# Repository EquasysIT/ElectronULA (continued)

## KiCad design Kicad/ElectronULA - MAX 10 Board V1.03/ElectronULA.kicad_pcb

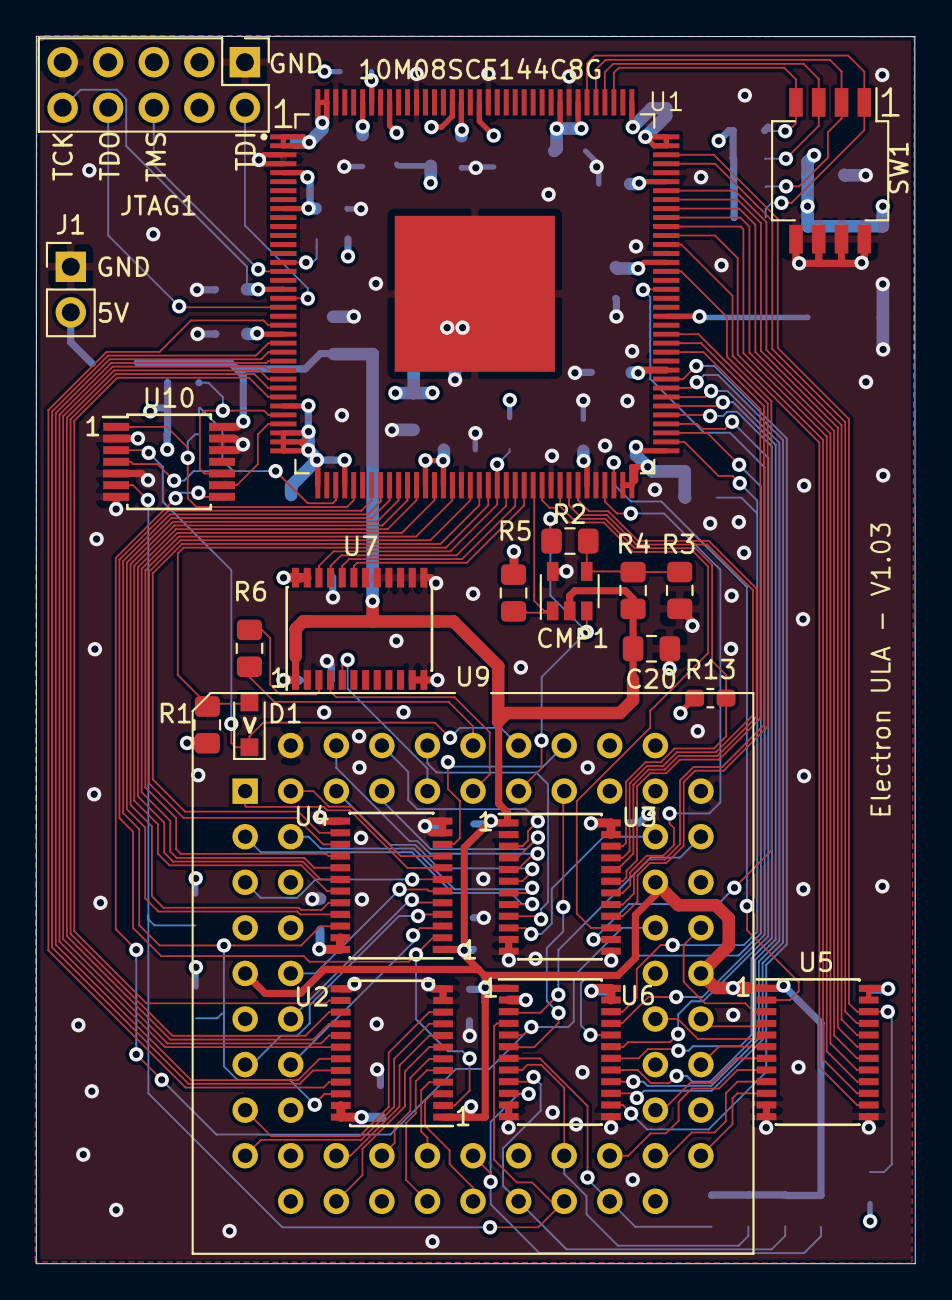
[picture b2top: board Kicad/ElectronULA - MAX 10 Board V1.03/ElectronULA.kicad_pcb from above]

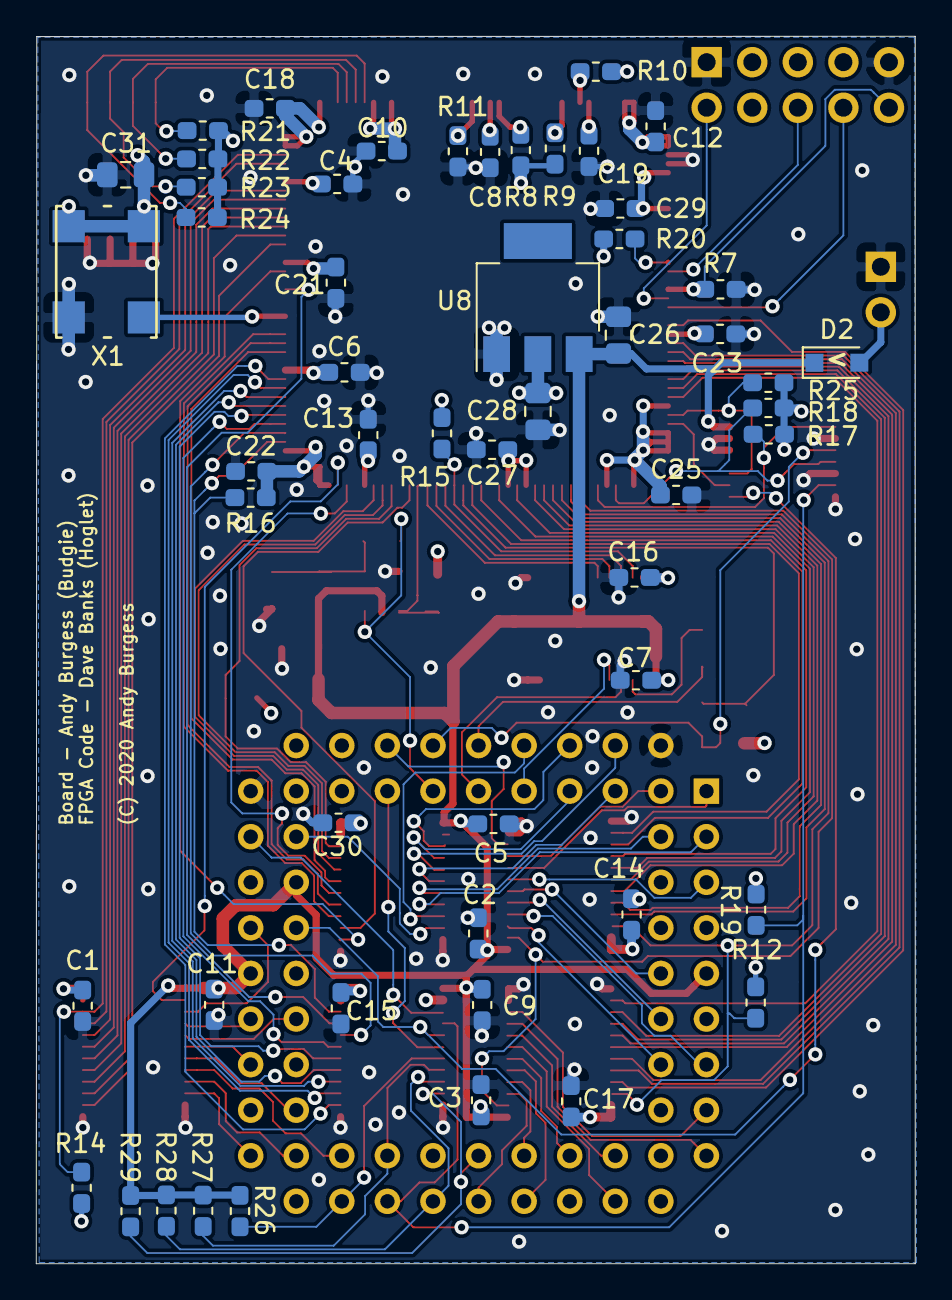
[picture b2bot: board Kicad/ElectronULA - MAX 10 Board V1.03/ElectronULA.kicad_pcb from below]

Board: 4 copper layers, 49.0 x 68.4 mm, 76 parts (54 on the bottom side), 121 nets.

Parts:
C1, C2, C3, C4, C5, C6, C7, C8, C9, C10, C11, C12, C13, C14, C15, C16, C17, C18, C19, C21, C22, C23, C25, C27, C29, C30: 0.1uf; C_0603_1608Metric_Pad1.05x0.95mm_HandSolder
C20: 0.1uf; C_0805_2012Metric_Pad1.15x1.40mm_HandSolder
C26, C31: 0.1uF; C_0805_2012Metric_Pad1.15x1.40mm_HandSolder
C28: 10uF; C_0805_2012Metric_Pad1.15x1.40mm_HandSolder
CMP1: MIC7221YM5-TR; SOT-23-5
D1, D2: D_Schottky_Small; D_SOD-323_HandSoldering
J1: Conn_01x02; PinHeader_1x02_P2.54mm_Vertical
JTAG1: Conn_02x05_Odd_Even; PinHeader_2x05_P2.54mm_Vertical
R1, R2, R3, R4, R5: 10K; R_0805_2012Metric_Pad1.15x1.40mm_HandSolder
R6: 100; R_0805_2012Metric_Pad1.15x1.40mm_HandSolder
R7, R8, R9, R10, R11, R12, R13, R14, R15, R16, R17, R18, R19, R20, R21, R22, R23, R24, R25: 10K; R_0603_1608Metric_Pad1.05x0.95mm_HandSolder
R26, R27, R28, R29: 4.7K; R_0603_1608Metric_Pad1.05x0.95mm_HandSolder
SW1: SW_DIP_x04; SW_DIP_SPSTx04_Slide_Copal_CHS-04B_W7.62mm_P1.27mm
U1: 10M08SCE144C8G; QFP50P2200X2200X165-145N
U2, U3, U4, U5, U6, U7: 74LVC4245APW; TSSOP-24_4.4x7.8mm_P0.65mm
U8: AP111733; SOT-223
U9: ELECTRON_ULA_PGA_68; PLCC-68_THT-Socket-Electron-ULA
U10: SN74HCT125D; TSSOP-14_4.4x5mm_P0.65mm
X1: OSC; Crystal_SMD_7050_4Pads

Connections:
/3V3: C1.1, C4.1, C6.1, C8.1, C10.1, C12.1, C13.1, C14.1, C15.1, C16.1, C17.1, C18.1, C19.1, C21.1, C22.1, C23.1, C25.1, C27.1, C28.1, C29.1, C30.1, C31.1, JTAG1.7, R1.2, R5.2, R8.1, R9.1, R10.1, R12.2, R13.2, R14.1, R15.2, R16.1, R17.2, R18.2, R19.2, R20.1, R21.2, R22.2, R23.2, R24.2, R25.2, U1.1, U1.2, U1.5, U1.9, U1.23, U1.31, U1.34, U1.35, U1.36, U1.37, U1.40, U1.49, U1.51, U1.67, U1.71, U1.72, U1.73, U1.82, U1.94, U1.103, U1.107, U1.108, U1.109, U1.115, U1.117, U1.128, U1.139, U1.143, U1.144, U2.23, U2.24, U3.23, U3.24, U4.23, U4.24, U5.23, U5.24, U6.2, U6.23, U6.24, U7.23, U7.24, U8.2, X1.1, X1.4
/5V: C2.1, C3.1, C5.1, C7.1, C9.1, C11.1, C20.2, C26.1, CMP1.2, D2.1, R4.2, R26.2, R27.2, R28.2, R29.2, U2.1, U3.1, U4.1, U5.1, U6.1, U7.1, U8.3, U9.9, U9.43, U9.48, U10.14
/5VP: D2.2, J1.2
/A0: U4.7, U9.5
/A1: U4.8, U9.1
/A2: U4.5, U9.12
/A3: U2.5, U9.24
/A4: U2.8, U9.21
/A5: U2.7, U9.20
/A6: U2.9, U9.17
/A7: U2.10, U9.15
/A8: U4.9, U9.2
/A9: U2.3, U9.26
/A10: U2.4, U9.25
/A11: U2.6, U9.23
/A12: U4.4, U9.13
/A13: U4.3, U9.14
/A14: U4.6, U9.10
/A15: U4.10, U9.56
/A_DIR: U1.43, U2.2, U4.2
/A_OE: R12.1, U1.44, U2.22, U4.22
/BLUE: U3.5, U9.66
/CAPS: U7.5, U9.63
/CASIN: CMP1.3, R2.1, U9.59
/CASMO: U3.3, U9.64
/CAS_OUT: U3.10, U9.50
/CLK_IN: U6.3, U9.49
/CONFIG_SEL: R11.2, U1.126
/CONF_DONE: R10.2, U1.138
/CSYNC: U3.4, U9.65
/G1_OE: R13.1, U1.64, U3.22
/G3_OE: R15.1, U1.57, U7.22
/G4_OE: R16.2, U1.74, U6.22
/GND: C1.2, C2.2, C3.2, C4.2, C5.2, C6.2, C7.2, C8.2, C9.2, C10.2, C11.2, C12.2, C13.2, C14.2, C15.2, C16.2, C17.2, C18.2, C19.2, C20.1, C21.2, C22.2, C23.2, C25.2, C26.2, C27.2, C28.2, C29.2, C30.2, C31.2, CMP1.5, J1.1, JTAG1.1, JTAG1.9, R3.1, R7.1, R11.1, SW1.5, SW1.6, SW1.7, SW1.8, U1.3, U1.4, U1.42, U1.53, U1.63, U1.68, U1.83, U1.95, U1.104, U1.116, U1.125, U1.133, U1.137, U1.142, U1.145, U2.11, U2.12, U2.13, U3.2, U3.11, U3.12, U3.13, U4.11, U4.12, U4.13, U5.11, U5.12, U5.13, U6.11, U6.12, U6.13, U7.2, U7.11, U7.12, U7.13, U7.14, U7.15, U7.16, U7.17, U7.18, U8.1, U9.51, U9.68, U10.2, U10.5, U10.7, U10.12, U10.13, X1.2
/GREEN: U3.7, U9.4
/JTAGEN: R20.2, U1.15
/KBD0: R29.1, U6.10, U9.27
/KBD1: R28.1, U6.9, U9.28
/KBD2: R27.1, U6.8, U9.31
/KBD3: R26.1, U6.7, U9.32
/LVA0: U1.50, U4.17
/LVA1: U1.52, U4.16
/LVA2: U1.47, U4.19
/LVA3: U1.25, U2.19
/LVA4: U1.28, U2.16
/LVA5: U1.27, U2.17
/LVA6: U1.29, U2.15
/LVA7: U1.30, U2.14
/LVA8: U1.54, U4.15
/LVA9: U1.22, U2.21
/LVA10: U1.24, U2.20
/LVA11: U1.26, U2.18
/LVA12: U1.46, U4.20
/LVA13: U1.45, U4.21
/LVA14: U1.48, U4.18
/LVA15: U1.55, U4.14
/LVBLUE: U1.84, U3.19
/LVCAPS: U1.60, U7.19
/LVCASIN: CMP1.1, R5.1, U1.61
/LVCASMO: U1.65, U3.21
/LVCAS_OUT: U1.93, U3.14
/LVCLK_IN: U1.91, U6.21
/LVCSYNC: U1.66, U3.20
/LVGREEN: U1.85, U3.17
/LVKBD0: U1.81, U6.14
/LVKBD1: U1.80, U6.15
/LVKBD2: U1.79, U6.16
/LVKBD3: U1.78, U6.17
/LVPD0: U1.98, U5.16
/LVPD1: U1.96, U5.14
/LVPD2: U1.97, U5.15
/LVPD3: U1.99, U5.17
/LVPD4: U1.100, U5.18
/LVPD5: U1.102, U5.20
/LVPD6: U1.101, U5.19
/LVPD7: U1.105, U5.21
/LVPHIOUT: U1.58, U7.21
/LVRED: U1.86, U3.16
/LVROM: U1.59, U7.20
/LVRSTOUT: R17.1, U1.41, U10.1
/LVRnWIN: U1.76, U6.19
/LVRnWOE: R25.1, U1.32, U10.10
/LVRnWOUT: U1.33, U10.9
/LVSND: U1.62, U3.15
/LVnHS: U1.69, U3.18
/LVnIRQIN: U1.75, U6.20
/LVnIRQOUT: R18.1, U1.39, U10.4
/LVnNMI: U1.77, U6.18
/OSC: U1.88, X1.3
/PD0: U5.8, U9.33
/PD1: U5.10, U9.35
/PD2: U5.9, U9.36
/PD3: U5.7, U9.38
/PD4: U5.6, U9.39
/PD5: U5.4, U9.41
/PD6: U5.5, U9.42
/PD7: U5.3, U9.45
/PD_DIR: U1.70, U5.2
/PD_OE: R14.2, U1.106, U5.22
/PHIOUT: R6.2, U9.60
/RED: U3.8, U9.3
/RESET: D1.1, U9.58, U10.3
/ROM: U7.4, U9.61
/RnW: U6.5, U9.46, U10.8
/SND: U3.9, U9.62
/SWC1: R24.1, SW1.1, U1.114
/SWC2: R23.1, SW1.2, U1.113
/SWC3: R22.1, SW1.3, U1.112
/SWC4: R21.1, SW1.4, U1.111
/TCK: JTAG1.10, R7.2, U1.18
/TDI: JTAG1.2, U1.19
/TDO: JTAG1.8, U1.20
/TMS: JTAG1.6, U1.16
/nCONFIG: R8.2, U1.129
/nHS: U3.6, U9.67
/nIRQ: R19.1, U6.4, U9.30, U10.6
/nNMI: U6.6, U9.57
/nRSTIN: D1.2, R1.1, U1.56
/nSTATUS: R9.2, U1.136
unnamed: CMP1.4, R2.2, R3.2, R4.1
unnamed: R6.1, U7.3

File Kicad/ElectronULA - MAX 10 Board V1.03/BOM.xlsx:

Acorn Electron ULA - MAX 10 Board - V1.03
Bill of Materials
Note: This board can only be fitted to a PGA68 socket on the Electron board. Th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
https://www.ebay.co.uk/i/292483310138?chn=ps&norover=1&mkevt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
Tips
1. Fit the ULA socket pins last (15). I would recommend "tinning" the pins whic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
2. Soldering the MAX 10 FPGA - Place a small amount of solder paste on the larg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
3. I recommend using a gel like flux for the SMD chips. Run plenty along each r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
4. All the passives (capacitors, resistors), comparator and regulator etc are b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
Excellent drag soldering guide here "https://www.youtube.com/watch?v=nyele3CIs-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
Id | Designator | Package | Quantity | Designation | Description | Supplier and ref
1 | R29,R28,R27,R26 | R_0603_1608Metric_Pad1.05x0.95mm_HandSolder | 4 | 4.7K Resistor | Pullups for Keyboard input
2 | D2,D1 | D_SOD-323_HandSoldering | 2 | Schottky Diode | BAT54 | https://www.digikey.co.uk/product-detail/en/on-semiconductor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
3 | U10 | TSSOP-14_4.4x5mm_P0.65mm | 1 | 74HCT125D | Quad Buffer | https://www.digikey.co.uk/product-detail/en/nexperia-usa-inc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,118/172…
4 | R25,R20,R24,R23,R22,R21,R19,R18,R17,R16,R15,R14,R13,R12,R11,R10,R9,R8,R7 | R_0603_1608Metric_Pad1.05x0.95mm_HandSolder | 19 | 10K Resistor
5 | SW1 | SW_DIP_SPSTx04_Slide_Copal_CHS-04B_W7.62mm_P1.27mm | 1 | SW_DIP_x04 | Configuration Switch | https://www.digikey.co.uk/product-detail/en/nidec-copal-elec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
6 | J1 | PinHeader_1x02_P2.54mm_Vertical | 1 | Conn_01x02 | 5V Power Input Normal Square Pins
7 | JTAG1 | PinHeader_2x05_P2.54mm_Vertical | 1 | Conn_02x05_Odd_Even | JTAG Pins Normal Square Pins
8 | C29,C27,C25,C23,C22,C21,C19,C18,C13,C12,C10,C8,C6,C4,C9,C7,C5,C3,C2,C11,C16,C30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 | C_0603_1608Metric_Pad1.05x0.95mm_HandSolder | 26 | 0.1uf Capacitor
9 | X1 | Crystal_SMD_7050_4Pads | 1 | Oscillator | 16Mhz Oscillator | Not required unless Electron 16Mhz signal is very poor. FPGA will require an up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
10 | C28 | C_0805_2012Metric_Pad1.15x1.40mm_HandSolder | 1 | 10uF Capacitor Tantalum
11 | U8 | SOT-223 | 1 | AP2114H-3.3TRG1 | Regulator | https://www.digikey.co.uk/product-detail/en/diodes-incorpora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
12 | C20,C26,C31 | C_0805_2012Metric_Pad1.15x1.40mm_HandSolder | 3 | 0.1uf Capacitor
13 | R2,R1,R5,R4,R3 | R_0805_2012Metric_Pad1.15x1.40mm_HandSolder | 5 | 10K Resistor
14 | U1 | EQFP | 1 | 10M08SCE144C8G | Intel MAX 10 FPGA | https://www.digikey.co.uk/products/en?keywords=10M08SCE144C8G
15 | U5,U7,U3,U6,U4,U2 | TSSOP-24_4.4x7.8mm_P0.65mm | 6 | 74LVC4245APW | Octal Transceiver | https://www.digikey.co.uk/product-detail/en/nexperia-usa-inc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
16 | U9 | ULA Socket Pins - 1x40 - 2.54mm Pin Headers | 2 | PGA 68 Pin Layout | ULA Socket Pins Turned Pin Type | https://hobbycomponents.com/connectors/439-01-254mm-40way-si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
17 | CMP1 | SOT-23-5 | 1 | MIC7221YM5-TR | Comparator | https://www.digikey.co.uk/product-detail/en/microchip-techno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
18 | R6 | R_0805_2012Metric_Pad1.15x1.40mm_HandSolder | 1 | 100R Resistor

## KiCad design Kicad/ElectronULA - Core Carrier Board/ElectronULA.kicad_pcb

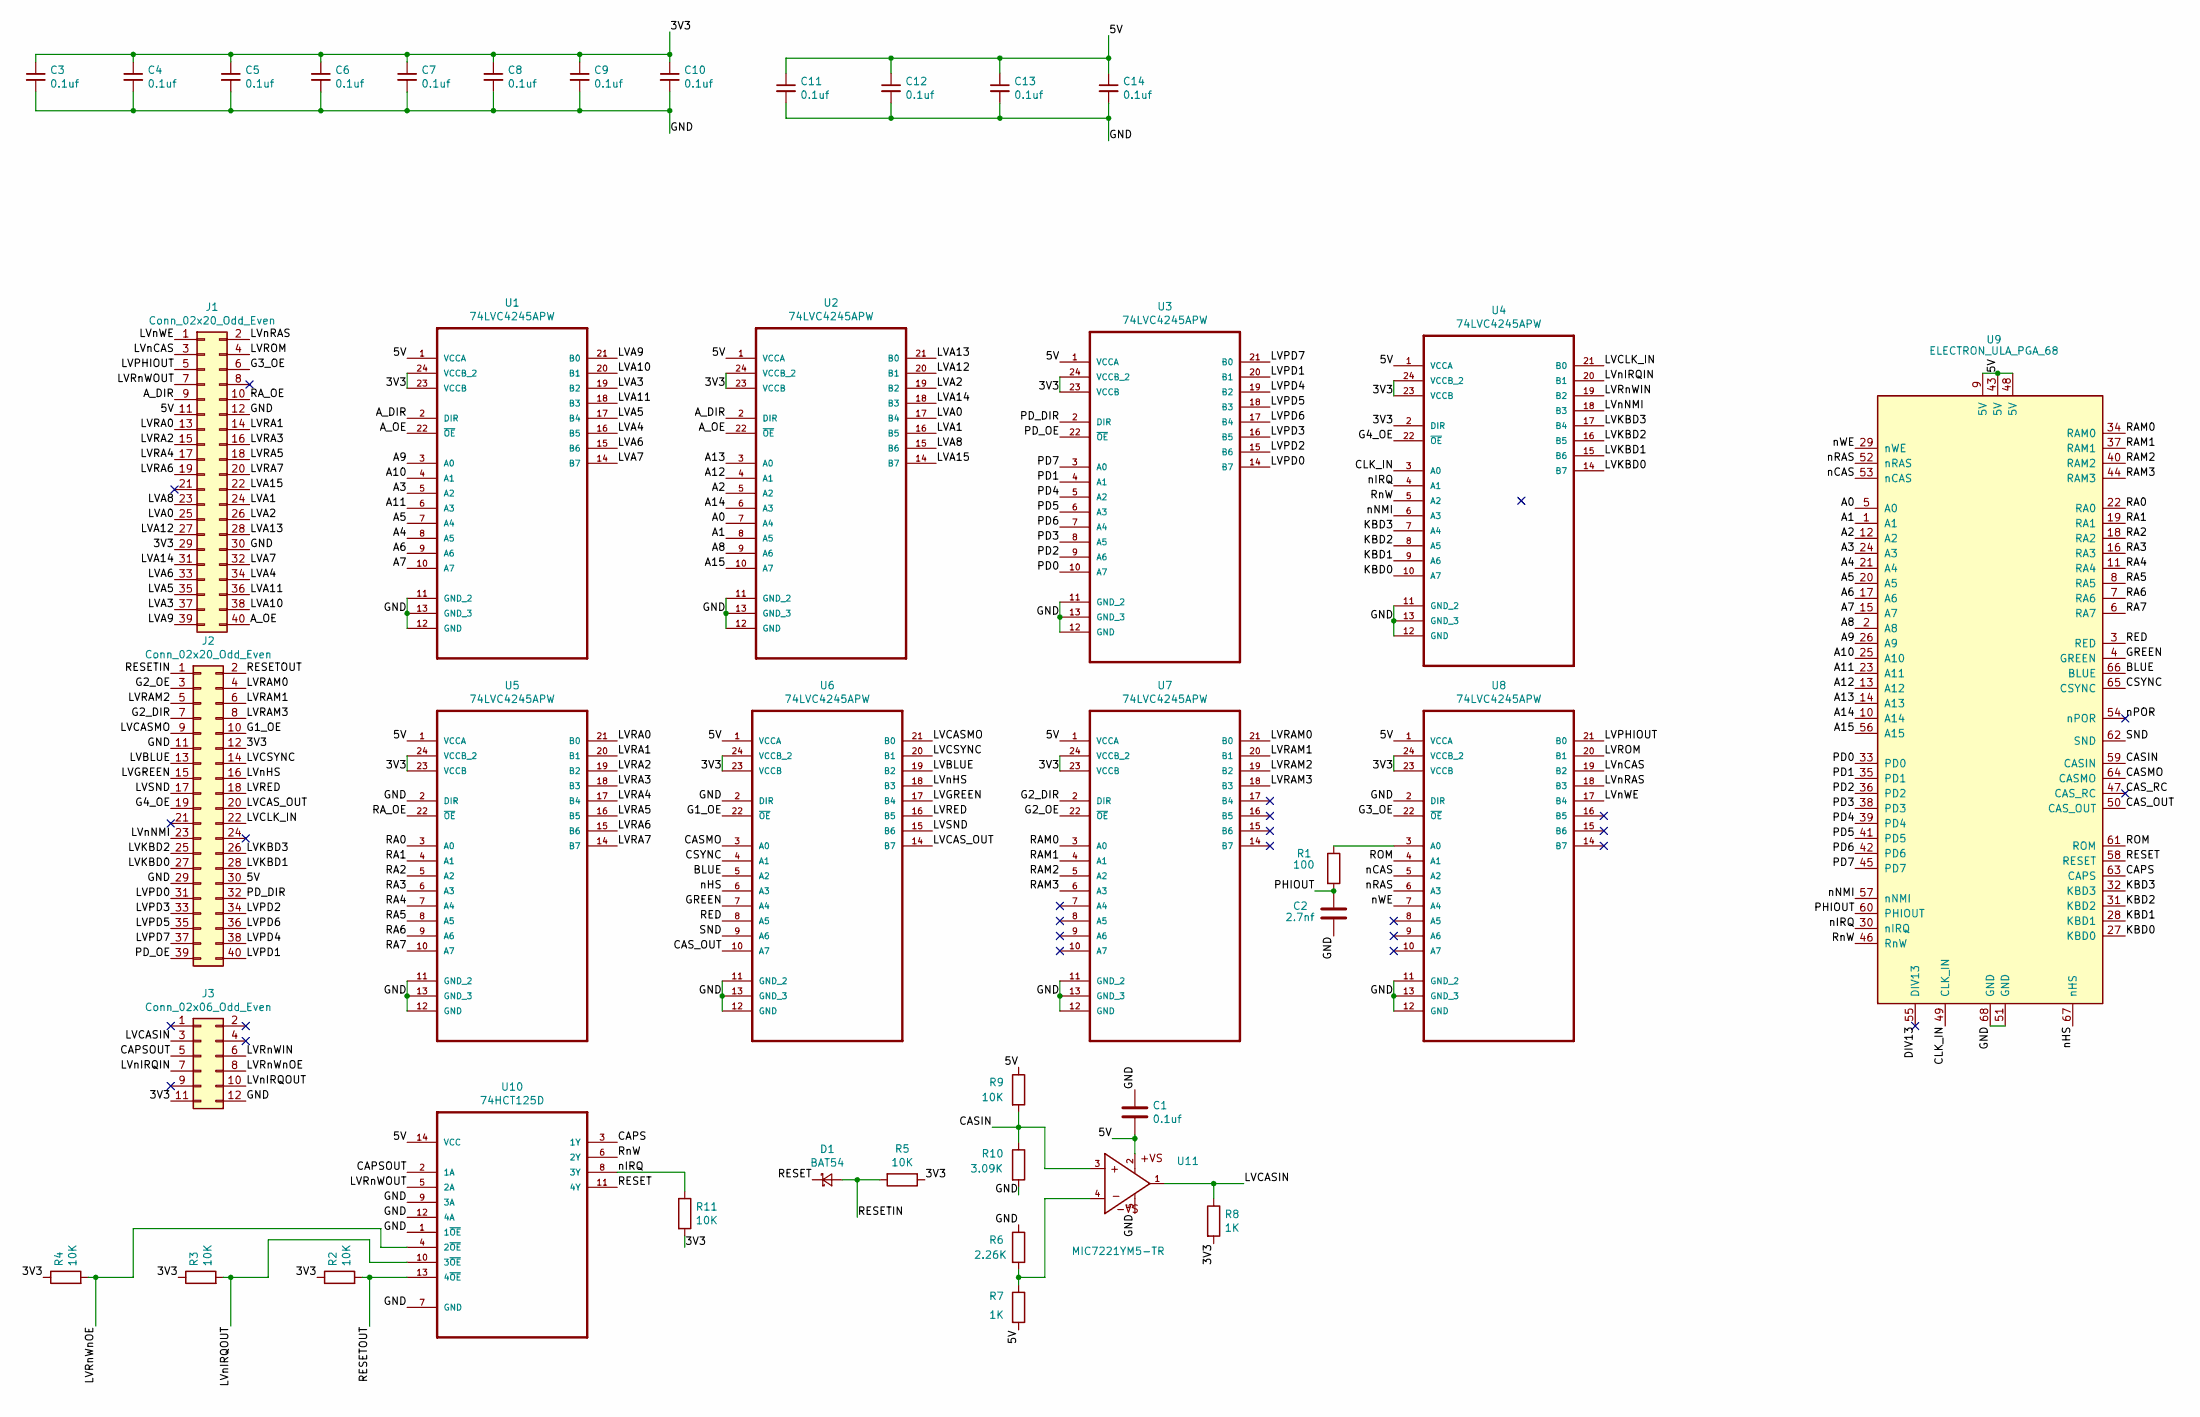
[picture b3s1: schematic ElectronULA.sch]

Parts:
C1: 0.1uf; C_0805_2012Metric_Pad1.15x1.40mm_HandSolder
C2: 2.7nf; C_0805_2012Metric_Pad1.15x1.40mm_HandSolder
C3, C4, C5, C6, C7, C8, C9, C10, C11, C12, C13, C14: 0.1uf; C_0603_1608Metric_Pad1.05x0.95mm_HandSolder
D1: BAT54; D_SOD-323_HandSoldering
J1, J2: Conn_02x20_Odd_Even; PinSocket_2x20_P2.54mm_Vertical
J3: Conn_02x06_Odd_Even; PinSocket_2x06_P2.54mm_Vertical
R1: 100; R_0805_2012Metric_Pad1.15x1.40mm_HandSolder
R2, R3, R4, R5, R9, R11: 10K; R_0805_2012Metric_Pad1.15x1.40mm_HandSolder
R6: 2.26K; R_0805_2012Metric_Pad1.15x1.40mm_HandSolder
R7, R8: 1K; R_0805_2012Metric_Pad1.15x1.40mm_HandSolder
R10: 3.09K; R_0805_2012Metric_Pad1.15x1.40mm_HandSolder
U1, U2, U3, U4, U5, U6, U7, U8: 74LVC4245APW; TSSOP-24_4.4x7.8mm_P0.65mm
U9: ELECTRON_ULA_PGA_68; PLCC-68_THT-Socket-Electron-ULA
U10: 74HCT125D; TSSOP-14_4.4x5mm_P0.65mm
U11: MIC7221YM5-TR; SOT-23-5

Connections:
/3V3: C3.1, C4.1, C5.1, C6.1, C7.1, C8.1, C9.1, C10.1, J1.29, J2.12, J3.11, R2.1, R3.1, R4.1, R5.1, R8.2, R11.2, U1.23 (VCCB), U1.24 (VCCB_2), U2.23 (VCCB), U2.24 (VCCB_2), U3.23 (VCCB), U3.24 (VCCB_2), U4.2 (DIR), U4.23 (VCCB), U4.24 (VCCB_2), U5.23 (VCCB), U5.24 (VCCB_2), U6.23 (VCCB), U6.24 (VCCB_2), U7.23 (VCCB), U7.24 (VCCB_2), U8.23 (VCCB), U8.24 (VCCB_2)
/5V: C1.2, C11.1, C12.1, C13.1, C14.1, J1.11, J2.30, R7.2, R9.1, U1.1 (VCCA), U2.1 (VCCA), U3.1 (VCCA), U4.1 (VCCA), U5.1 (VCCA), U6.1 (VCCA), U7.1 (VCCA), U8.1 (VCCA), U9.9 (5V), U9.43 (5V), U9.48 (5V), U10.14 (VCC), U11.2 (+VS)
/A0: U2.7 (A4), U9.5 (A0)
/A1: U2.8 (A5), U9.1 (A1)
/A2: U2.5 (A2), U9.12 (A2)
/A3: U1.5 (A2), U9.24 (A3)
/A4: U1.8 (A5), U9.21 (A4)
/A5: U1.7 (A4), U9.20 (A5)
/A6: U1.9 (A6), U9.17 (A6)
/A7: U1.10 (A7), U9.15 (A7)
/A8: U2.9 (A6), U9.2 (A8)
/A9: U1.3 (A0), U9.26 (A9)
/A10: U1.4 (A1), U9.25 (A10)
/A11: U1.6 (A3), U9.23 (A11)
/A12: U2.4 (A1), U9.13 (A12)
/A13: U2.3 (A0), U9.14 (A13)
/A14: U2.6 (A3), U9.10 (A14)
/A15: U2.10 (A7), U9.56 (A15)
/A_DIR: J1.9, U1.2 (DIR), U2.2 (DIR)
/A_OE: J1.40, U1.22 (~OE), U2.22 (~OE)
/BLUE: U6.5 (A2), U9.66 (BLUE)
/CAPS: U9.63 (CAPS), U10.3 (1Y)
/CAPSOUT: J3.5, U10.2 (1A)
/CASIN: R9.2, R10.1, U9.59 (CASIN), U11.3 (IN+)
/CASMO: U6.3 (A0), U9.64 (CASMO)
/CAS_OUT: U6.10 (A7), U9.50 (CAS_OUT)
/CAS_RC: U9.47 (CAS_RC)
/CLK_IN: U4.3 (A0), U9.49 (CLK_IN)
/CSYNC: U6.4 (A1), U9.65 (CSYNC)
/DIV13: U9.55 (DIV13)
/G1_OE: J2.10, U6.22 (~OE)
/G2_DIR: J2.7, U7.2 (DIR)
/G2_OE: J2.3, U7.22 (~OE)
/G3_OE: J1.6, U8.22 (~OE)
/G4_OE: J2.19, U4.22 (~OE)
/GND: C1.1, C2.2, C3.2, C4.2, C5.2, C6.2, C7.2, C8.2, C9.2, C10.2, C11.2, C12.2, C13.2, C14.2, J1.12, J1.30, J2.11, J2.29, J3.12, R6.1, R10.2, U1.11 (GND_2), U1.12 (GND), U1.13 (GND_3), U2.11 (GND_2), U2.12 (GND), U2.13 (GND_3), U3.11 (GND_2), U3.12 (GND), U3.13 (GND_3), U4.11 (GND_2), U4.12 (GND), U4.13 (GND_3), U5.2 (DIR), U5.11 (GND_2), U5.12 (GND), U5.13 (GND_3), U6.2 (DIR), U6.11 (GND_2), U6.12 (GND), U6.13 (GND_3), U7.11 (GND_2), U7.12 (GND), U7.13 (GND_3), U8.2 (DIR), U8.11 (GND_2), U8.12 (GND), U8.13 (GND_3), U9.51 (GND), U9.68 (GND), U10.1 (1~OE), U10.7 (GND), U10.9 (3A), U10.12 (4A), U11.5 (-VS)
/GREEN: U6.7 (A4), U9.4 (GREEN)
/KBD0: U4.10 (A7), U9.27 (KBD0)
/KBD1: U4.9 (A6), U9.28 (KBD1)
/KBD2: U4.8 (A5), U9.31 (KBD2)
/KBD3: U4.7 (A4), U9.32 (KBD3)
/LVA0: J1.25, U2.17 (B4)
/LVA1: J1.24, U2.16 (B5)
/LVA2: J1.26, U2.19 (B2)
/LVA3: J1.37, U1.19 (B2)
/LVA4: J1.34, U1.16 (B5)
/LVA5: J1.35, U1.17 (B4)
/LVA6: J1.33, U1.15 (B6)
/LVA7: J1.32, U1.14 (B7)
/LVA8: J1.23, U2.15 (B6)
/LVA9: J1.39, U1.21 (B0)
/LVA10: J1.38, U1.20 (B1)
/LVA11: J1.36, U1.18 (B3)
/LVA12: J1.27, U2.20 (B1)
/LVA13: J1.28, U2.21 (B0)
/LVA14: J1.31, U2.18 (B3)
/LVA15: J1.22, U2.14 (B7)
/LVBLUE: J2.13, U6.19 (B2)
/LVCASIN: J3.3, R8.1, U11.1 (OUT)
/LVCASMO: J2.9, U6.21 (B0)
/LVCAS_OUT: J2.20, U6.14 (B7)
/LVCLK_IN: J2.22, U4.21 (B0)
/LVCSYNC: J2.14, U6.20 (B1)
/LVGREEN: J2.15, U6.17 (B4)
/LVKBD0: J2.27, U4.14 (B7)
/LVKBD1: J2.28, U4.15 (B6)
/LVKBD2: J2.25, U4.16 (B5)
/LVKBD3: J2.26, U4.17 (B4)
/LVPD0: J2.31, U3.14 (B7)
/LVPD1: J2.40, U3.20 (B1)
/LVPD2: J2.34, U3.15 (B6)
/LVPD3: J2.33, U3.16 (B5)
/LVPD4: J2.38, U3.19 (B2)
/LVPD5: J2.35, U3.18 (B3)
/LVPD6: J2.36, U3.17 (B4)
/LVPD7: J2.37, U3.21 (B0)
/LVPHIOUT: J1.5, U8.21 (B0)
/LVRA0: J1.13, U5.21 (B0)
/LVRA1: J1.14, U5.20 (B1)
/LVRA2: J1.15, U5.19 (B2)
/LVRA3: J1.16, U5.18 (B3)
/LVRA4: J1.17, U5.17 (B4)
/LVRA5: J1.18, U5.16 (B5)
/LVRA6: J1.19, U5.15 (B6)
/LVRA7: J1.20, U5.14 (B7)
/LVRAM0: J2.4, U7.21 (B0)
/LVRAM1: J2.6, U7.20 (B1)
/LVRAM2: J2.5, U7.19 (B2)
/LVRAM3: J2.8, U7.18 (B3)
/LVRED: J2.18, U6.16 (B5)
/LVROM: J1.4, U8.20 (B1)
/LVRnWIN: J3.6, U4.19 (B2)
/LVRnWOUT: J1.7, U10.5 (2A)
/LVRnWnOE: J3.8, R4.2, U10.4 (2~OE)
/LVSND: J2.17, U6.15 (B6)
/LVnCAS: J1.3, U8.19 (B2)
/LVnHS: J2.16, U6.18 (B3)
/LVnIRQIN: J3.7, U4.20 (B1)
/LVnIRQOUT: J3.10, R3.2, U10.10 (3~OE)
/LVnNMI: J2.23, U4.18 (B3)
/LVnRAS: J1.2, U8.18 (B3)
/LVnWE: J1.1, U8.17 (B4)
/PD0: U3.10 (A7), U9.33 (PD0)
/PD1: U3.4 (A1), U9.35 (PD1)
/PD2: U3.9 (A6), U9.36 (PD2)
/PD3: U3.8 (A5), U9.38 (PD3)
/PD4: U3.5 (A2), U9.39 (PD4)
/PD5: U3.6 (A3), U9.41 (PD5)
/PD6: U3.7 (A4), U9.42 (PD6)
/PD7: U3.3 (A0), U9.45 (PD7)
/PD_DIR: J2.32, U3.2 (DIR)
/PD_OE: J2.39, U3.22 (~OE)
/PHIOUT: C2.1, R1.2, U9.60 (PHIOUT)
/RA0: U5.3 (A0), U9.22 (RA0)
/RA1: U5.4 (A1), U9.19 (RA1)
/RA2: U5.5 (A2), U9.18 (RA2)
/RA3: U5.6 (A3), U9.16 (RA3)
/RA4: U5.7 (A4), U9.11 (RA4)
/RA5: U5.8 (A5), U9.8 (RA5)
/RA6: U5.9 (A6), U9.7 (RA6)
/RA7: U5.10 (A7), U9.6 (RA7)
/RAM0: U7.3 (A0), U9.34 (RAM0)
/RAM1: U7.4 (A1), U9.37 (RAM1)
/RAM2: U7.5 (A2), U9.40 (RAM2)
/RAM3: U7.6 (A3), U9.44 (RAM3)
/RA_OE: J1.10, U5.22 (~OE)
/RED: U6.8 (A5), U9.3 (RED)
/RESET: D1.1 (K), U9.58 (RESET), U10.11 (4Y)
/RESETIN: D1.2 (A), J2.1, R5.2
/RESETOUT: J2.2, R2.2, U10.13 (4~OE)
/ROM: U8.4 (A1), U9.61 (ROM)
/RnW: U4.5 (A2), U9.46 (RnW), U10.6 (2Y)
/SND: U6.9 (A6), U9.62 (SND)
/nCAS: U8.5 (A2), U9.53 (nCAS)
/nHS: U6.6 (A3), U9.67 (nHS)
/nIRQ: R11.1, U4.4 (A1), U9.30 (nIRQ), U10.8 (3Y)
/nNMI: U4.6 (A3), U9.57 (nNMI)
/nPOR: U9.54 (nPOR)
/nRAS: U8.6 (A3), U9.52 (nRAS)
/nWE: U8.7 (A4), U9.29 (nWE)
unnamed: R1.1, U8.3 (A0)
unnamed: R6.2, R7.1, U11.4 (IN-)

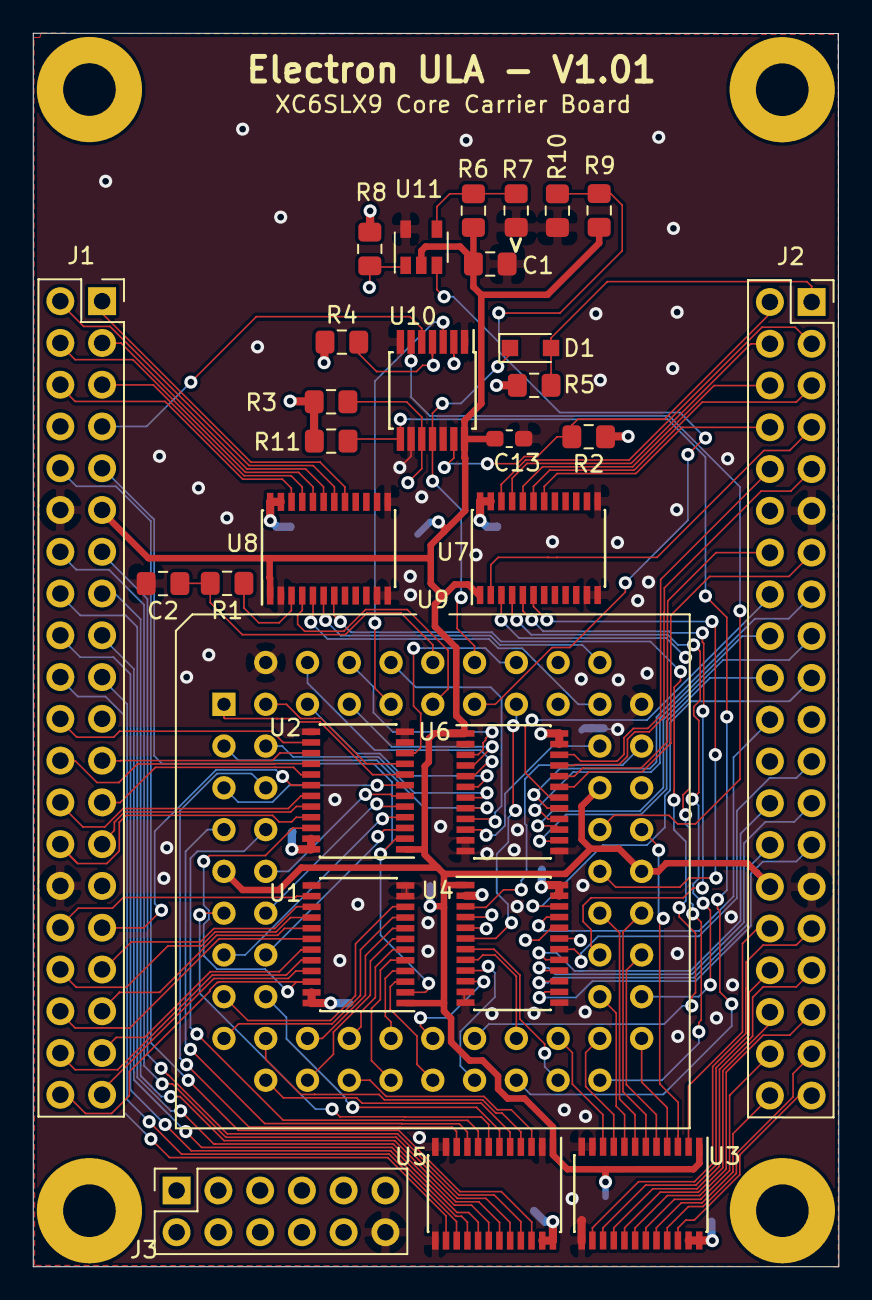
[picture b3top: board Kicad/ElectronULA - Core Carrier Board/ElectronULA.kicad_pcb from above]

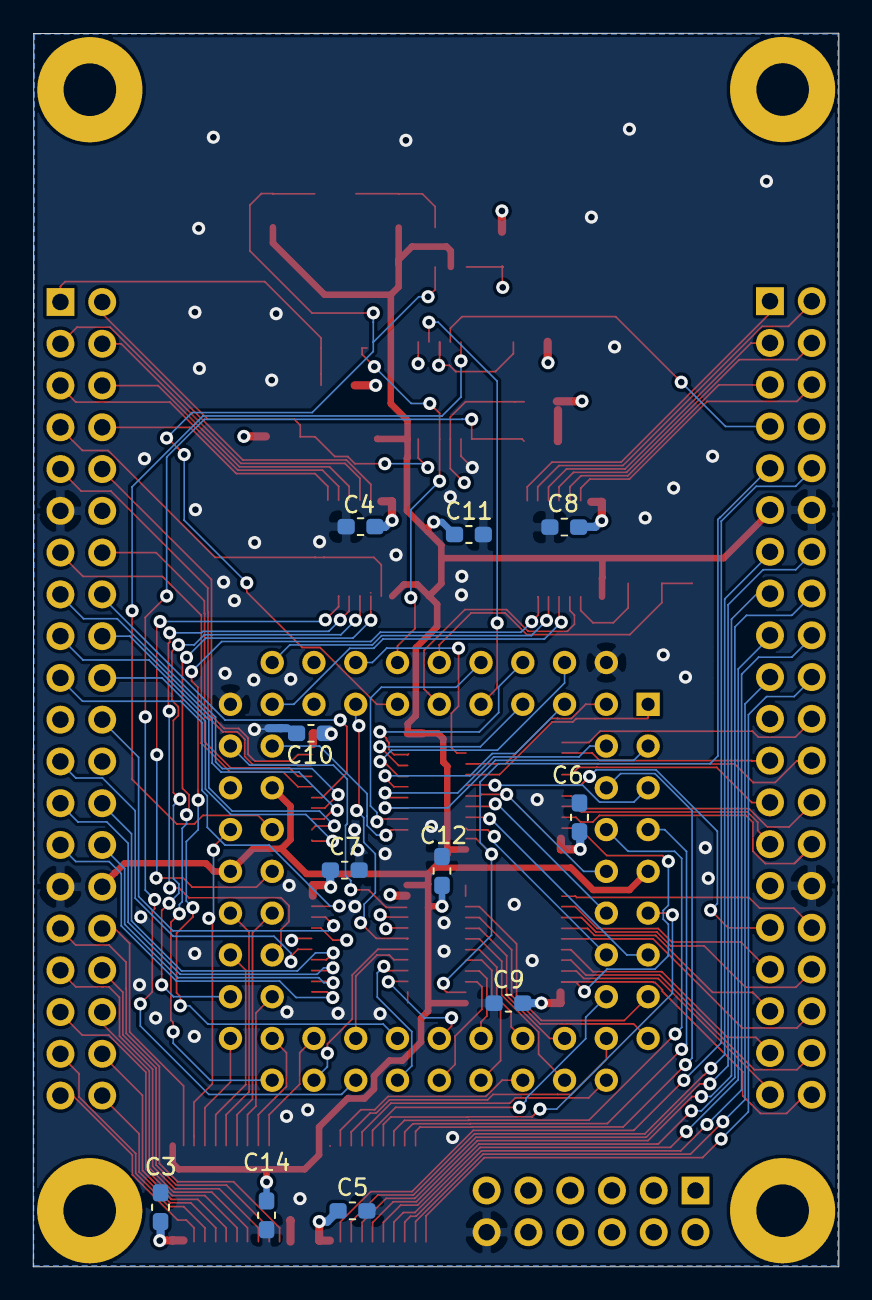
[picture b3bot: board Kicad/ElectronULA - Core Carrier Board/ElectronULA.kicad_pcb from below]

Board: 4 copper layers, 49.0 x 75.0 mm, 44 parts (11 on the bottom side), 139 nets.

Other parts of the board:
H2, H2#2, H2#3, H2#4: MountingHole_Pad; MountingHole_3.2mm_M3_Pad

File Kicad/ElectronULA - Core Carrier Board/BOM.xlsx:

Electron ULA Core Carrier Board BOM
Item | Size | Qty | Part | Comment
100R Resistor | 0805 | 1 | R1
10K Resistor | 0805 | 6 | R2,R3,R4,R5,R9,R11
2.26K Resistor | 0805 | 1 | R6
3.09K Resistor | 0805 | 1 | R10
1K Resistor | 0805 | 2 | R7, R8
0.1uf Capacitor | 0805 | 1 | C1
2.7nf Capacitor | 0805 | 1 | C2
0.1uf Capacitor | 0603 | 12 | C3-C14
BAT54 Diode | SOD-323 | 1 | D1 | https://www.digikey.co.uk/product-detail/en/on-semiconductor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
2x40 Female Headers | 2.54mm | 2
2x6 Female Headers | 2.54mm | 1
74LVC4245A | TSSOP24 | 8 | Octal Transceiver | https://www.digikey.co.uk/product-detail/en/nexperia-usa-inc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
74HCT125 | TSSOP14 | 1 | Quad Buffer | https://www.digikey.co.uk/product-detail/en/nexperia-usa-inc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
MIC7221YM5-TR | SOT-23-5 | 1 | Comparator | https://www.digikey.co.uk/product-detail/en/microchip-techno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
1x32 - 2.54mm Low Profile Pin Headers |  | 3 | Pins for ULA socket | https://www.toby.co.uk/board-to-board-pcb-connectors/254mm-h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
 |  |  |  | 5

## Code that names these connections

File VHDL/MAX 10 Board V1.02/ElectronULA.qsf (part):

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
set_location_assignment PIN_39 -to nIRQOUT
set_location_assignment PIN_75 -to nIRQIN
set_location_assignment PIN_43 -to A_DIR
set_location_assignment PIN_44 -to A_OE
set_location_assignment PIN_56 -to nRSTIN
set_location_assignment PIN_41 -to nRSTOUT
set_location_assignment PIN_57 -to G3_OE
set_location_assignment PIN_58 -to clk_out
set_location_assignment PIN_59 -to ROM_n
set_location_assignment PIN_60 -to caps
set_location_assignment PIN_61 -to casIn
set_location_assignment PIN_70 -to PD_DIR
set_location_assignment PIN_74 -to G4_OE
set_location_assignment PIN_91 -to clk_in
set_location_assignment PIN_76 -to RnWIN
set_location_assignment PIN_33 -to RnWOUT
set_location_assignment PIN_32 -to RnWOE
#set_location_assignment PIN_77 -to nNMI
set_location_assignment PIN_78 -to kbd[3]
set_location_assignment PIN_79 -to kbd[2]
set_location_assignment PIN_80 -to kbd[1]
set_location_assignment PIN_81 -to kbd[0]
set_location_assignment PIN_62 -to sound
set_location_assignment PIN_64 -to G1_OE
set_location_assignment PIN_65 -to casMO
set_location_assignment PIN_66 -to csync
set_location_assignment PIN_88 -to osc
set_location_assignment PIN_84 -to blue
set_location_assignment PIN_69 -to nhs
set_location_assignment PIN_85 -to green
set_location_assignment PIN_86 -to red
set_location_assignment PIN_93 -to casOut
set_location_assignment PIN_106 -to PD_OE



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
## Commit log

2020-06-03 Added "All in one MAX 10" board
2020-06-19 Added latest ver 1.02 board
2020-06-19 Create LICENSE
2020-06-20 Updated BOM
2020-06-22 Added VHDL
2020-06-25 Updated BOM to provide technique for soldering the MAX 10 FPGA
2020-06-26 Added 4.7K pullups for the keyboard Inputs
2020-06-26 Folder rename
2020-06-26 Cleared Gerbers
2020-06-29 Update .qsf file to include Switch connections
2020-07-03 Latest changes added from Hoglet - ROM chip found to work at 4Mhz
2020-07-05 Fix for UFM SAA5050 Char ROM Initialisation
2020-07-05 Update clks
2020-07-19 Fixed RSTIN
2020-07-28 Updated with changes from Hoglet
    Fix for 0xC0DE's vertical rupture test (a6ce79a) and transparent latch fix (af6c24e)
2020-08-21 Added controlling of CPU Speed & Interlacing via switches
2021-01-30 Added latest V1.03 Gerbers
2021-06-19 Added build file for immediate programming to MAX10 FPGA
2022-03-15 Added version 1.04 of PCB
2022-03-19 Latest updates for 1.04
2023-01-16 Update ElectronULA.vhd
    Changes to fix bus contention issues
2023-01-17 Fix databus contention issues
    Updated buffer control to fix databus contention issues
2023-07-07 Updated with latest VHDL and Kicad Ver 1.05 Board
2023-07-12 Latest version 1.05 with keyboard glitch fix
2023-07-14 Update to latest FPGA pof file
2023-07-15 Update Gerbers
2023-08-21 Tidy Comments
2025-09-27 Added files to enable direct compiling in Quartus
